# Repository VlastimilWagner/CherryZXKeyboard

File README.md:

# CherryZXKeyboard

The goal of the project was to create a keyboard consisting of Cherry MX keys with two-layer keycaps, into which printed labels will be inserted. At the same time, I wanted the keyboard to have a better layout of the keys (for example, cursor keys), to be easy to manufacture and install (ideally without SMD), from available components, cheap and at the same time to write well on it.

I wasn't limited to a standard format as the goal was to build a ZX MAX 128 clone and put it in my own cabinet.

Since the ZX Spectrum+ membrane is double-layered, the 48p-KDLX solution was suitable, i.e. electronically secured switching of two contacts at the same time, since the MX buttons have only one contact.

## What is needed to make

### PCB
In the [Gerber](/Gerber) directory there are materials for production. For example, on [https://jlcpcb.com](https://jlcpcb.com), just pack this directory in ZIP format, insert it into the order, and after payment, you have printed circuit boards within 2 weeks, even with the cheapest selected transport.

### Electronic Parts
These are common cheap parts from a local dealer - for example TME.
* 30 pcs Diode BAT42
* 1 pc Electrolytic capacitor 10u
* 5 pcs Resistor network (6x-1-104LF) 
* 5 pcs 74HC4066
* 5 pcs DIP14 socket

### Mechanical MX Switches (62 pcs) [AliExpress](https://www.aliexpress.com/item/1005004285423123.html )
You can use the original, but rather expensive Cherry MX, or, like me, a copy of the MX switches from AliExpress.

### Keycaps
Three types of keycaps are used:

#### - Standard buttons (53 pcs) [AliExpress](https://www.aliexpress.com/item/1005004623750938.html )

#### - Wide buttons (4 pcs) [AliExpress](https://www.aliexpress.com/item/1005003201365793.html )

#### - Space bar 6.25u (1 pc) [AliExpress](https://www.aliexpress.com/item/1005003211865080.html )

### Mechanical stabilizer for spacebar 6.25u (1 pc) [AliExpress](https://www.aliexpress.com/item/1005002552011081.html )

### 3D printed inserts
I divided the printing of the mat into 2 parts so that it would not be a problem to print it on a standard size 3D printer. The documents in STL format are in the [Stl](./Stl) directory.

### Labels
The labels were drawn in Inkscape and can be printed on any color printer on plain office paper. File in SVG format is in [Labels](./Labels) directory.

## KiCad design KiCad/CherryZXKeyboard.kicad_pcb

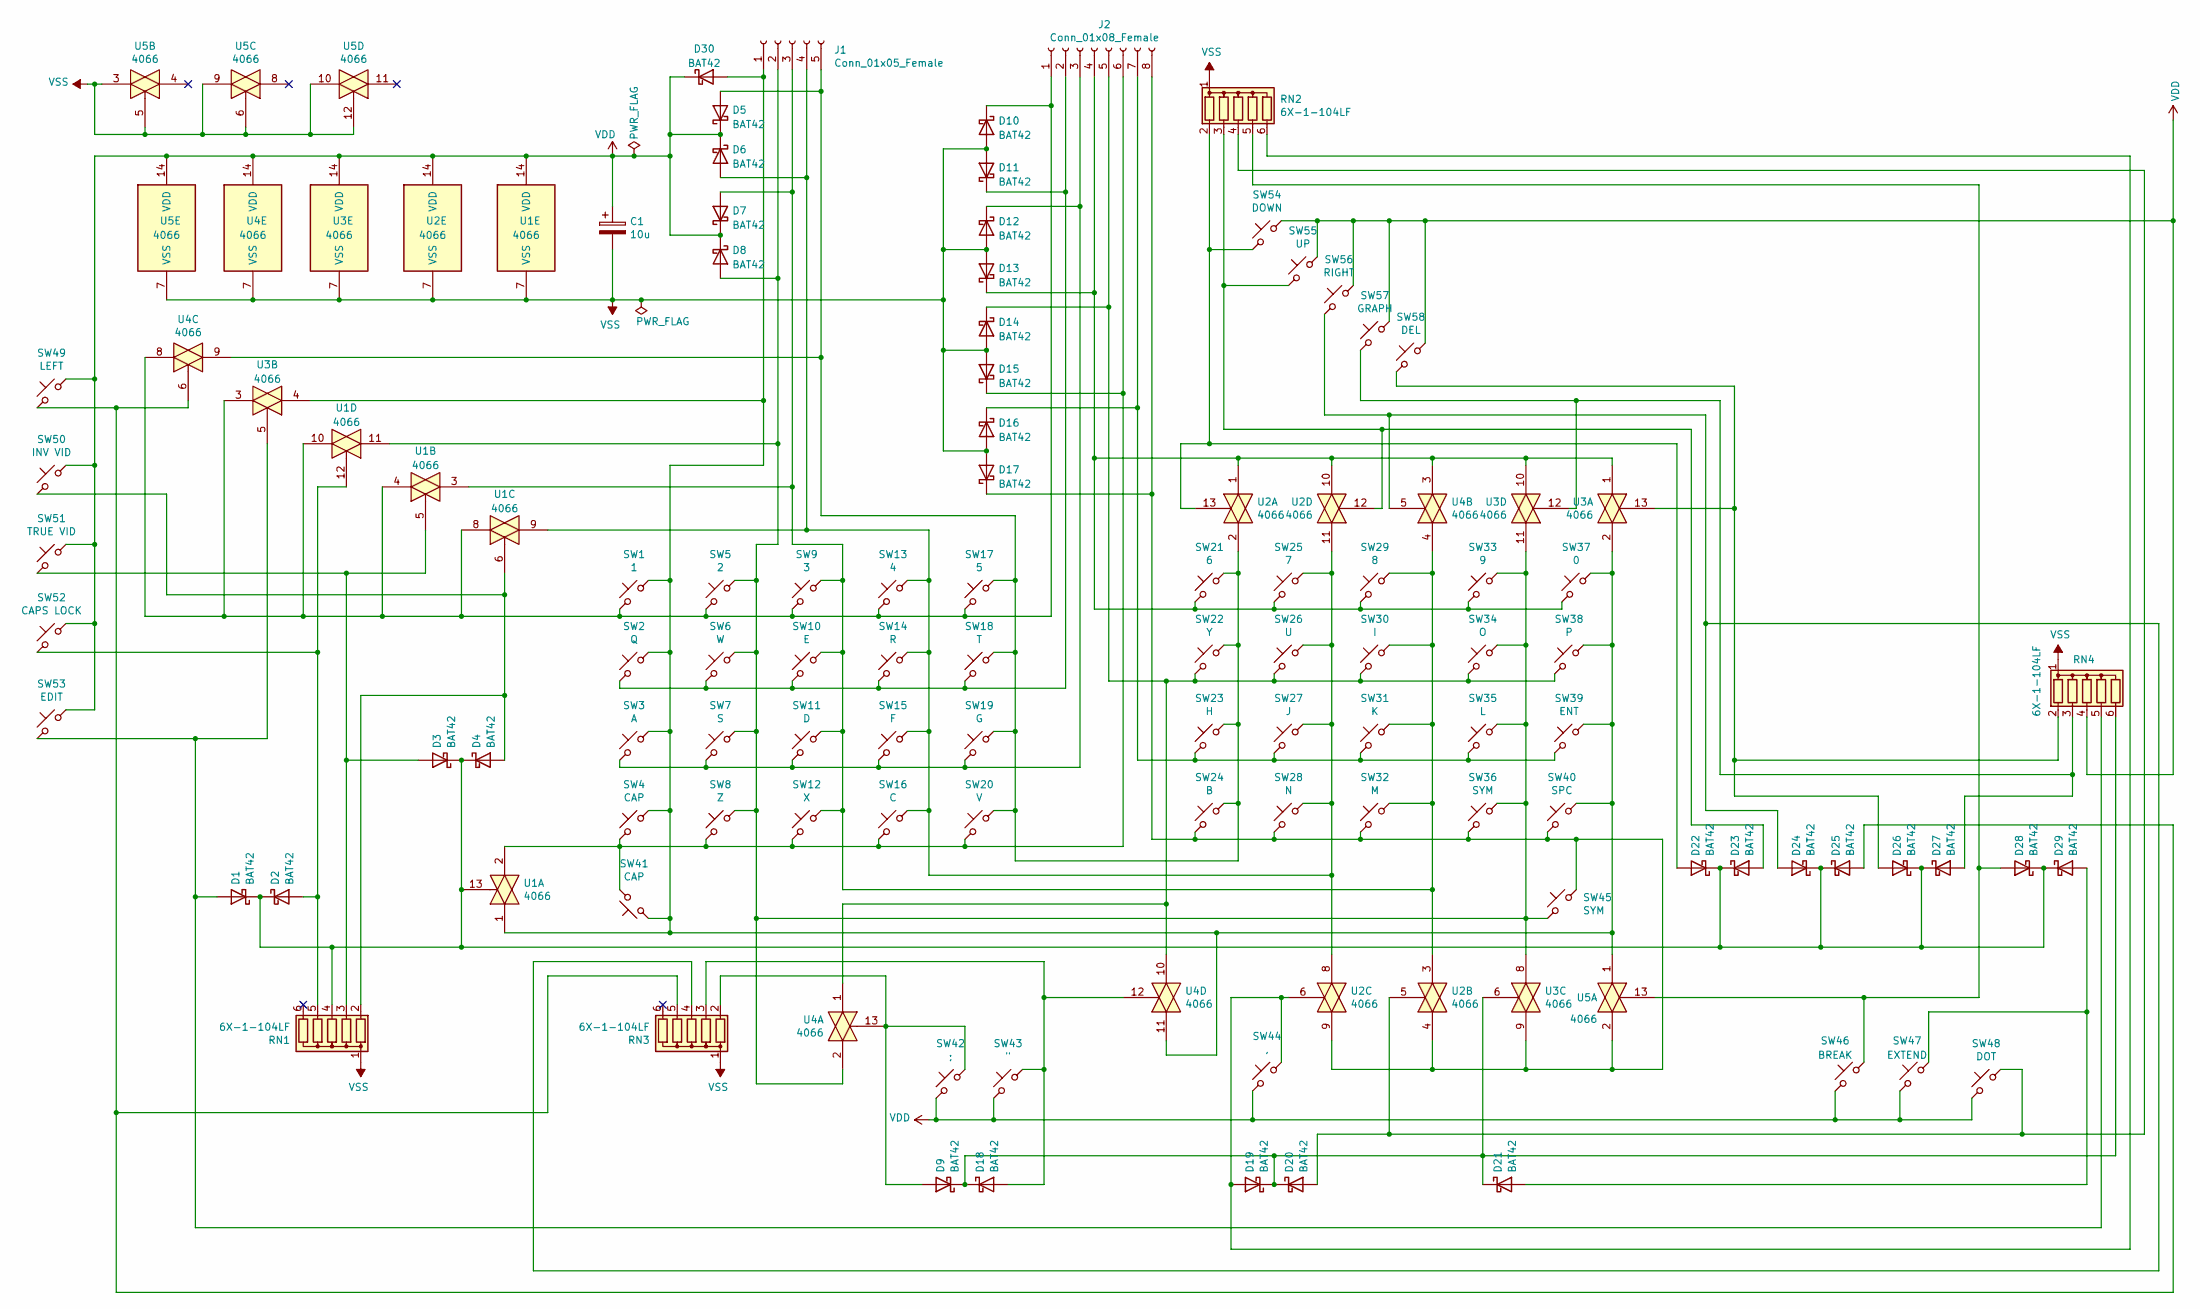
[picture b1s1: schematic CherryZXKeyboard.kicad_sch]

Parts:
C1: 10u; CP_Radial_D5.0mm_P2.50mm
D1, D2, D3, D4, D5, D6, D7, D8, D9, D10, D11, D12, D13, D14, D15, D16, D17, D18, D19, D20, D21, D22, D23, D24, D25, D26, D27, D28, D29, D30: BAT42; D_DO-35_SOD27_P7.62mm_Horizontal
J1: Conn_01x05_Female; PinHeader_1x05_P2.54mm_Vertical
J2: Conn_01x08_Female; PinHeader_1x08_P2.54mm_Vertical
RN1, RN2, RN3, RN4: 6X-1-104LF; R_Array_SIP6
SW1: 1; SW_Cherry_MX_1.00u_PCB
SW2: Q; SW_Cherry_MX_1.00u_PCB
SW3: A; SW_Cherry_MX_1.00u_PCB
SW4, SW41: CAP; SW_Cherry_MX_1.00u_PCB
SW5: 2; SW_Cherry_MX_1.00u_PCB
SW6: W; SW_Cherry_MX_1.00u_PCB
SW7: S; SW_Cherry_MX_1.00u_PCB
SW8: Z; SW_Cherry_MX_1.00u_PCB
SW9: 3; SW_Cherry_MX_1.00u_PCB
SW10: E; SW_Cherry_MX_1.00u_PCB
SW11: D; SW_Cherry_MX_1.00u_PCB
SW12: X; SW_Cherry_MX_1.00u_PCB
SW13: 4; SW_Cherry_MX_1.00u_PCB
SW14: R; SW_Cherry_MX_1.00u_PCB
SW15: F; SW_Cherry_MX_1.00u_PCB
SW16: C; SW_Cherry_MX_1.00u_PCB
SW17: 5; SW_Cherry_MX_1.00u_PCB
SW18: T; SW_Cherry_MX_1.00u_PCB
SW19: G; SW_Cherry_MX_1.00u_PCB
SW20: V; SW_Cherry_MX_1.00u_PCB
SW21: 6; SW_Cherry_MX_1.00u_PCB
SW22: Y; SW_Cherry_MX_1.00u_PCB
SW23: H; SW_Cherry_MX_1.00u_PCB
SW24: B; SW_Cherry_MX_1.00u_PCB
SW25: 7; SW_Cherry_MX_1.00u_PCB
SW26: U; SW_Cherry_MX_1.00u_PCB
SW27: J; SW_Cherry_MX_1.00u_PCB
SW28: N; SW_Cherry_MX_1.00u_PCB
SW29: 8; SW_Cherry_MX_1.00u_PCB
SW30: I; SW_Cherry_MX_1.00u_PCB
SW31: K; SW_Cherry_MX_1.00u_PCB
SW32: M; SW_Cherry_MX_1.00u_PCB
SW33: 9; SW_Cherry_MX_1.00u_PCB
SW34: O; SW_Cherry_MX_1.00u_PCB
SW35: L; SW_Cherry_MX_1.00u_PCB
SW36, SW45: SYM; SW_Cherry_MX_1.00u_PCB
SW37: 0; SW_Cherry_MX_1.00u_PCB
SW38: P; SW_Cherry_MX_1.00u_PCB
SW39: ENT; SW_Cherry_MX_1.00u_PCB
SW40: SPC; SW_Cherry_MX_1.00u_PCB
SW42: ;; SW_Cherry_MX_1.00u_PCB
SW43: "; SW_Cherry_MX_1.00u_PCB
SW44: ,; SW_Cherry_MX_1.00u_PCB
SW46: BREAK; SW_Cherry_MX_1.00u_PCB
SW47: EXTEND; SW_Cherry_MX_1.00u_PCB
SW48: DOT; SW_Cherry_MX_1.00u_PCB
SW49: LEFT; SW_Cherry_MX_1.00u_PCB
SW50: INV VID; SW_Cherry_MX_1.00u_PCB
SW51: TRUE VID; SW_Cherry_MX_1.00u_PCB
SW52: CAPS LOCK; SW_Cherry_MX_1.00u_PCB
SW53: EDIT; SW_Cherry_MX_1.00u_PCB
SW54: DOWN; SW_Cherry_MX_1.00u_PCB
SW55: UP; SW_Cherry_MX_1.00u_PCB
SW56: RIGHT; SW_Cherry_MX_1.00u_PCB
SW57: GRAPH; SW_Cherry_MX_1.00u_PCB
SW58: DEL; SW_Cherry_MX_1.00u_PCB
U1, U2, U3, U4, U5: 4066; DIP-14_W7.62mm_LongPads

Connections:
unnamed: D1.1 (K), D2.1 (K), D3.1 (K), D4.1 (K), D22.1 (K), D23.1 (K), D24.1 (K), D25.1 (K), D26.1 (K), D27.1 (K), D28.1 (K), D29.1 (K), RN1.4 (R3), U1.13
unnamed: D1.2 (A), RN4.5 (R4), SW53.2, U3.5
unnamed: D2.2 (A), RN1.5 (R4), SW52.2, U1.12
unnamed: D3.2 (A), RN1.3 (R2), SW51.2, U1.5
unnamed: D5.2 (A), J1.5, SW17.1, SW18.1, SW19.1, SW20.1, SW21.1, SW22.1, SW23.1, SW24.1, U2.2, U4.9
unnamed: D6.2 (A), J1.4, SW13.1, SW14.1, SW15.1, SW16.1, SW25.1, SW26.1, SW27.1, SW28.1, U1.9, U2.8, U2.11
unnamed: D7.2 (A), J1.3, SW9.1, SW10.1, SW11.1, SW12.1, SW29.1, SW30.1, SW31.1, SW32.1, U1.3, U2.3, U4.4
unnamed: D8.2 (A), J1.2, SW5.1, SW6.1, SW7.1, SW8.1, SW33.1, SW34.1, SW35.1, SW36.1, SW45.1, U1.11, U3.8, U3.11, U4.2
unnamed: D9.2 (A), RN3.2 (R1), SW42.1, U4.13
unnamed: D10.1 (K), J2.1, SW1.2, SW5.2, SW9.2, SW13.2, SW17.2, U1.4, U1.8, U1.10, U3.3, U4.8
unnamed: D11.1 (K), J2.2, SW2.2, SW6.2, SW10.2, SW14.2, SW18.2
unnamed: D12.1 (K), J2.3, SW3.2, SW7.2, SW11.2, SW15.2, SW19.2
unnamed: D13.1 (K), J2.4, SW21.2, SW25.2, SW29.2, SW33.2, SW37.2, U2.1, U2.10, U3.1, U3.10, U4.3
unnamed: D14.1 (K), J2.5, SW22.2, SW26.2, SW30.2, SW34.2, SW38.2, U4.1, U4.10
unnamed: D15.1 (K), J2.6, SW4.2, SW8.2, SW12.2, SW16.2, SW20.2, SW41.2, U1.2
unnamed: D16.1 (K), J2.7, SW23.2, SW27.2, SW31.2, SW35.2, SW39.2
unnamed: D17.1 (K), J2.8, SW24.2, SW28.2, SW32.2, SW36.2, SW40.2, SW45.2, U2.4, U2.9, U3.9, U5.2
unnamed: D9.1 (K), D18.1 (K), D19.1 (K), D20.1 (K), D21.1 (K), RN4.6 (R5), U3.6
unnamed: D18.2 (A), RN3.3 (R2), SW43.1, U4.12
unnamed: D19.2 (A), RN2.6 (R5), SW44.1, U2.6
unnamed: D20.2 (A), RN2.4 (R3), SW48.1, U2.5
unnamed: D21.2 (A), D29.2 (A), SW47.1
unnamed: D22.2 (A), RN2.2 (R1), SW54.2, U2.13
unnamed: D23.2 (A), RN2.3 (R2), SW55.2, U2.12
unnamed: D24.2 (A), RN3.4 (R3), SW56.2, U4.5
unnamed: D25.2 (A), RN3.5 (R4), SW49.2, U4.6
unnamed: D26.2 (A), RN4.2 (R1), SW58.2, U3.13
unnamed: D27.2 (A), RN4.3 (R2), SW57.2, U3.12
unnamed: D28.2 (A), RN2.5 (R4), SW46.1, U5.13
unnamed: D30.2 (A), J1.1, SW1.1, SW2.1, SW3.1, SW4.1, SW37.1, SW38.1, SW39.1, SW40.1, SW41.1, U1.1, U3.2, U3.4, U4.11, U5.1
unnamed: D4.2 (A), RN1.2 (R1), SW50.2, U1.6
VDD: C1.1, D5.1 (K), D6.1 (K), D7.1 (K), D8.1 (K), D30.1 (K), RN4.4 (R3), SW42.2, SW43.2, SW44.2, SW46.2, SW47.2, SW48.2, SW49.1, SW50.1, SW51.1, SW52.1, SW53.1, SW54.1, SW55.1, SW56.1, SW57.1, SW58.1, U1.14 (VDD), U2.14 (VDD), U3.14 (VDD), U4.14 (VDD), U5.14 (VDD)
VSS: C1.2, D10.2 (A), D11.2 (A), D12.2 (A), D13.2 (A), D14.2 (A), D15.2 (A), D16.2 (A), D17.2 (A), RN1.1 (common), RN2.1 (common), RN3.1 (common), RN4.1 (common), U1.7 (VSS), U2.7 (VSS), U3.7 (VSS), U4.7 (VSS), U5.3, U5.5, U5.6, U5.7 (VSS), U5.9, U5.10, U5.12

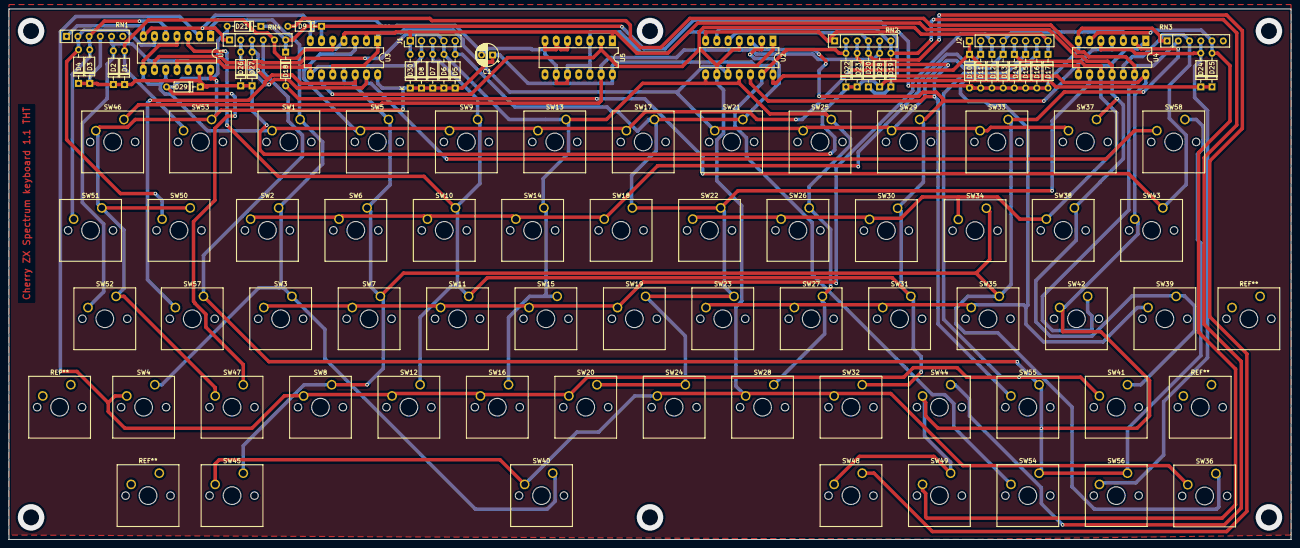
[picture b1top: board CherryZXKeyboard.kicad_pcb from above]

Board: 2 copper layers, 290.0 x 120.0 mm, 100 parts (0 on the bottom side), 33 nets.

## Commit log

2023-02-24 New files
